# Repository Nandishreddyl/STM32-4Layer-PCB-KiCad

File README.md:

# STM32F103C6T6 — Four-Layer PCB Design Using KiCad

## Project Overview

This project presents the schematic design and four-layer PCB layout of an STM32F103C6T6-based microcontroller board, developed using KiCad.

The board integrates a microcontroller, USB interface, power regulation, clock circuitry, reset and boot configuration, and external connector interfaces. The design workflow includes schematic capture, PCB component placement, copper routing, design-rule checking (DRC), and Gerber generation.

## Project Objectives

- Design a custom STM32-based microcontroller PCB.
- Create and organize the electronic schematic using KiCad.
- Develop a four-layer PCB layout with SMD components.
- Route electrical connections across the available copper layers.
- Generate manufacturing files for PCB fabrication.
- Prepare the design for future hardware prototyping and testing.

## Hardware and Components

| Component | Purpose |
|---|---|
| STM32F103C6T6 | Main microcontroller |
| AMS1117-1.5 | Voltage regulation stage, as labeled in the schematic |
| 16 MHz crystal | External clock source |
| USB Micro-B connector | USB interface and board power input |
| Capacitors | Decoupling and power-supply filtering |
| Resistors | Pull-up, configuration, and current-limiting functions |
| SPDT switch | Hardware configuration |
| Pin headers | External signal and power connections |
| Ferrite bead | Power-line filtering |

*Note: Verify the regulator output voltage and USB power arrangement against the final schematic before fabrication.*

## Design Tools

- **EDA Software:** KiCad
- **Schematic Design:** KiCad Schematic Editor
- **PCB Layout:** KiCad PCB Editor
- **Routing:** KiCad interactive routing and FreeRouting autorouter
- **Design Validation:** KiCad Electrical Rules Checker (ERC) and Design Rules Checker (DRC)
- **Manufacturing Outputs:** Gerber files and drill files

## Four-Layer PCB Stack-Up

The PCB is configured with four copper layers:

| Layer | Intended purpose |
|---|---|
| F.Cu | Component-side routing and signal connections |
| In1.Cu | Ground plane |
| In2.Cu | Power distribution and additional routing |
| B.Cu | Bottom-side signal routing |

The final copper-zone assignments and layer connectivity should be verified in the PCB project before manufacturing.

## PCB Design Workflow

1. Created the STM32 microcontroller schematic in KiCad.
2. Assigned component footprints and transferred the design to PCB Editor.
3. Arranged components and established the board layout.
4. Configured the four copper layers.
5. Routed connections using KiCad and FreeRouting.
6. Added vias to connect signals between copper layers where necessary.
7. Resolved design-rule violations, including via-diameter constraints and board-outline issues.
8. Generated Gerber and drill files for manufacturing preparation.

## Repository Contents

- `STM32_PCB.kicad_sch` — schematic source file
- `STM32_PCB.kicad_pcb` — PCB layout source file
- `STM32_PCB.kicad_pro` — KiCad project settings
- `Gerber/` — exported manufacturing files

## Design Validation

The PCB was checked using KiCad's Design Rules Checker. The reported DRC errors were resolved, and the latest check reported zero errors.

This confirms that the reported DRC checks passed at that stage; it does not independently verify electrical functionality or successful manufacturing.

## Current Project Status

**Status:** PCB layout and manufacturing-file preparation.

The schematic and PCB layout have been developed in KiCad. Physical fabrication, assembly, and hardware testing should be documented separately once completed.

## Future Improvements

- Fabricate the PCB and inspect manufacturing quality.
- Assemble the components and verify the power supply.
- Test the STM32 clock, reset, boot configuration, and USB interface.
- Validate the board using a multimeter and suitable debugging tools.
- Document measured results and update the design based on testing.

## Author

**Nandish Reddy L**

Electronics and Communication Engineering  
Interests: PCB Design, Embedded Systems, Digital VLSI, and Hardware Development.

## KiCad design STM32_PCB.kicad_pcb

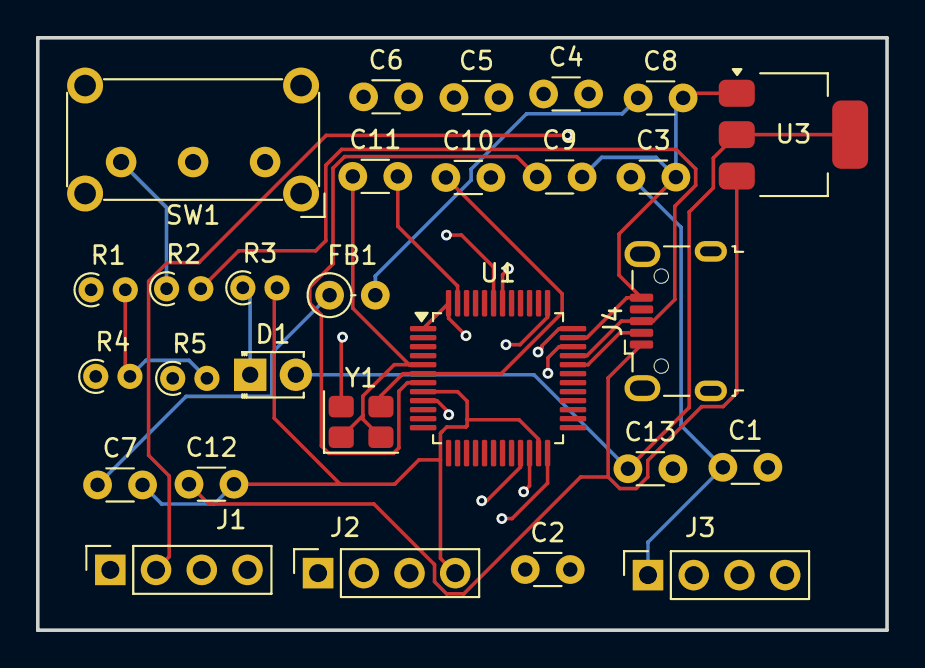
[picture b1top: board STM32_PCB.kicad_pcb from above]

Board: 4 copper layers, 47.2 x 32.9 mm, 28 parts (0 on the bottom side), 19 nets.

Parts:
C1, C2, C3, C4, C5, C9, C10, C11: 100n; C_Disc_D3.0mm_W1.6mm_P2.50mm
C6, C8: 1u; C_Disc_D3.0mm_W1.6mm_P2.50mm
C7: 10n; C_Disc_D3.0mm_W1.6mm_P2.50mm
C12, C13: 22u; C_Disc_D3.0mm_W1.6mm_P2.50mm
D1: red; LED_D1.8mm_W3.3mm_H2.4mm
FB1: 120R; L_Axial_L5.3mm_D2.2mm_P2.54mm_Vertical_Vishay_IM-1
J1, J2, J3: Conn_01x04_Pin; PinSocket_1x04_P2.54mm_Vertical
J4: USB_B_Micro; USB_Micro-B_Wuerth_629105150521
R1: 10K; R_Axial_DIN0204_L3.6mm_D1.6mm_P1.90mm_Vertical
R2, R3: 1.5k; R_Axial_DIN0204_L3.6mm_D1.6mm_P1.90mm_Vertical
R4, R5: 1.5K; R_Axial_DIN0204_L3.6mm_D1.6mm_P1.90mm_Vertical
SW1: SW_SPDT; SW_E-Switch_EG1224_SPDT_Angled
U1: STM32F103C6Tx; LQFP-48_7x7mm_P0.5mm
U3: AMS1117-1.5; SOT-223-3_TabPin2
Y1: 16MHZ; Crystal_SMD_3225-4Pin_3.2x2.5mm

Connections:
+3.3V: C1.1, C2.1, C3.1, C4.1, C5.1, J1.1, J2.1, J3.1, R1.2, R2.1, R4.2, R5.2, SW1.3 (C), U1.1 (VBAT), U1.24 (VDD), U1.36 (VDD), U1.48 (VDD)
+3.3VA: C6.1, C7.1, FB1.1, U1.9 (VDDA)
/HSE_IN: C11.1, U1.5 (PD0), Y1.1, Y1.2 (G)
/HSE_OUT: C10.1, U1.6 (PD1), Y1.3
/I2C2_SCL: J2.2, R4.1, U1.21 (PB10)
/I2C2_SDL: J2.3, R5.1, U1.22 (PB11)
/SWCLK: J3.3, U1.37 (PA14)
/SWDIO: J3.2, U1.34 (PA13)
/USART1_RX: J1.3, U1.43 (PB7)
/USART1_TX: J1.2, U1.42 (PB6)
/USB_D+: J4.3 (D+), R2.2, U1.33 (PA12)
/USB_D-: J4.2 (D-), U1.32 (PA11)
GND: C1.2, C2.2, C3.2, C4.2, C5.2, C6.2, C7.2, C8.2, C9.2, C10.2, C11.2, C12.2, C13.2, J1.4, J2.4, J3.4, J4.5 (GND), R3.2, SW1.1 (A), U1.8 (VSSA), U1.23 (VSS), U1.35 (VSS), U1.47 (VSS), U3.1 (GND), Y1.4 (G)
unnamed: C8.1, FB1.2
unnamed: C13.1, D1.2 (A), U3.2 (VO)
unnamed: D1.1 (K), R3.1
unnamed: R1.1, SW1.2 (B)
unnamed: C9.1, U1.7 (NRST)
VBUS: C12.1, J4.1 (VBUS), U3.3 (VI)
